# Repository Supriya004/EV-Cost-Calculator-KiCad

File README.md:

EV Cost Calculator — KiCad PCB Design

About the Project
This is a learning project created using KiCad 9 to practice electronic circuit design, PCB layout, component placement, and track routing for an EV Cost Calculator system.

Project Preview

Components Used
- Arduino UNO R3
- ACS712 current sensor
- Voltage sensor connector
- Temperature sensor connector
- 16x2 I²C LCD connector
- Relay
- LEDs and resistors
- Buzzer
- Push buttons

Tools Used
- KiCad 9 — schematic design and PCB layout

Project Status
The schematic and PCB layout were created for learning and practice. Some connections remain unrouted, so this design is **not a manufacturing-ready PCB**.

Files
-`cost_calculator.kicad_sch` — circuit schematic
- `cost_calculator.kicad_pcb` — PCB layout
- `cost_calculator.kicad_pro` — KiCad project settings

Created as a hands-on electronics design learning project.

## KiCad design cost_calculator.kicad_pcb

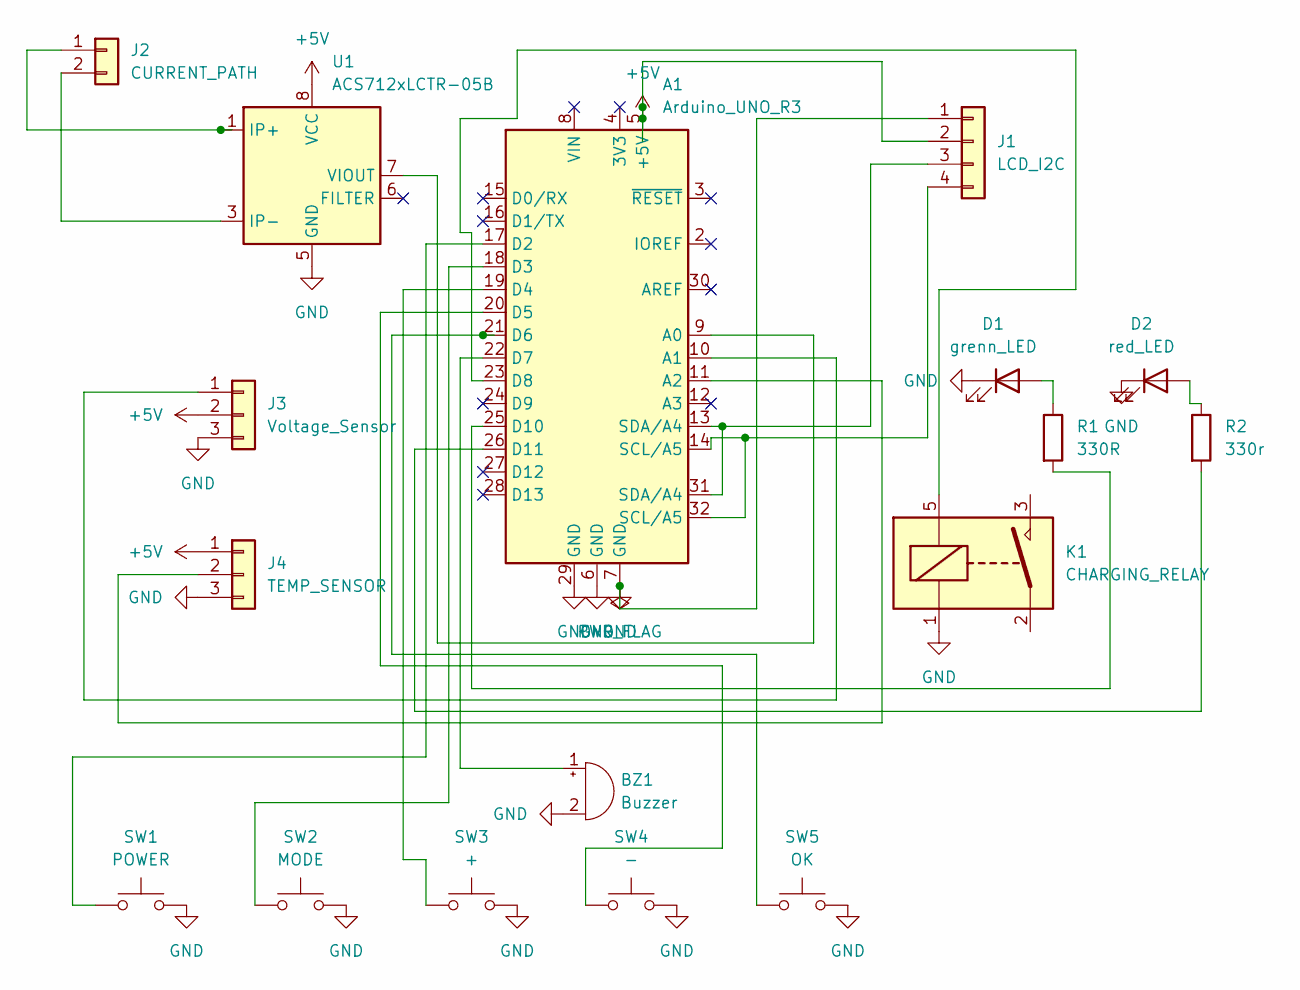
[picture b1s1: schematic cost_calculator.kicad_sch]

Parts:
A1: Arduino_UNO_R3; Arduino_UNO_R3_WithMountingHoles
BZ1: Buzzer; Buzzer_12x9.5RM7.6
D1: grenn_LED; LED_D5.0mm
D2: red_LED; LED_D5.0mm
J1: LCD_I2C; PinHeader_1x04_P2.54mm_Vertical
J2: CURRENT_PATH; PinHeader_1x02_P2.54mm_Vertical
J3: Voltage_Sensor; PinHeader_1x03_P2.54mm_Vertical
J4: TEMP_SENSOR; PinHeader_1x03_P2.54mm_Vertical
K1: CHARGING_RELAY; Relay_SPST_Omron-G5Q-1A
R1: 330R; R_Axial_DIN0207_L6.3mm_D2.5mm_P10.16mm_Horizontal
R2: 330r; R_Axial_DIN0207_L6.3mm_D2.5mm_P10.16mm_Horizontal
SW1: POWER; SW_PUSH_6mm
SW2: MODE; SW_PUSH_6mm
SW3: +; SW_PUSH_6mm
SW4: -; SW_PUSH_6mm
SW5: OK; SW_PUSH_6mm
U1: ACS712xLCTR-05B; SOIC-8_3.9x4.9mm_P1.27mm

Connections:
+5V: A1.5 (+5V), J1.2, J3.2, J4.1, U1.8 (VCC)
GND: A1.6 (GND), A1.7 (GND), A1.29 (GND), BZ1.2 (-), D1.1 (K), D2.1 (K), J1.1, J3.3, J4.3, K1.1, SW1.2, SW2.2, SW3.2, SW4.2, SW5.2, U1.5 (GND)
unnamed: A1.9 (A0), U1.7 (VIOUT)
unnamed: A1.10 (A1), J3.1
unnamed: A1.11 (A2), J4.2
unnamed: A1.17 (D2), SW1.1
unnamed: A1.18 (D3), SW2.1
unnamed: A1.19 (D4), SW3.1
unnamed: A1.20 (D5), SW4.1
unnamed: A1.21 (D6), SW5.1
unnamed: A1.22 (D7), BZ1.1 (+)
unnamed: A1.23 (D8), K1.5
unnamed: A1.25 (D10), R1.2
unnamed: A1.26 (D11), R2.2
unnamed: D1.2 (A), R1.1
unnamed: D2.2 (A), R2.1
unnamed: A1.13 (SDA/A4), A1.31 (SDA/A4), J1.3
unnamed: A1.14 (SCL/A5), A1.32 (SCL/A5), J1.4
unnamed: J2.1, U1.1 (IP+), U1.2 (IP+)
unnamed: J2.2, U1.3 (IP-), U1.4 (IP-)

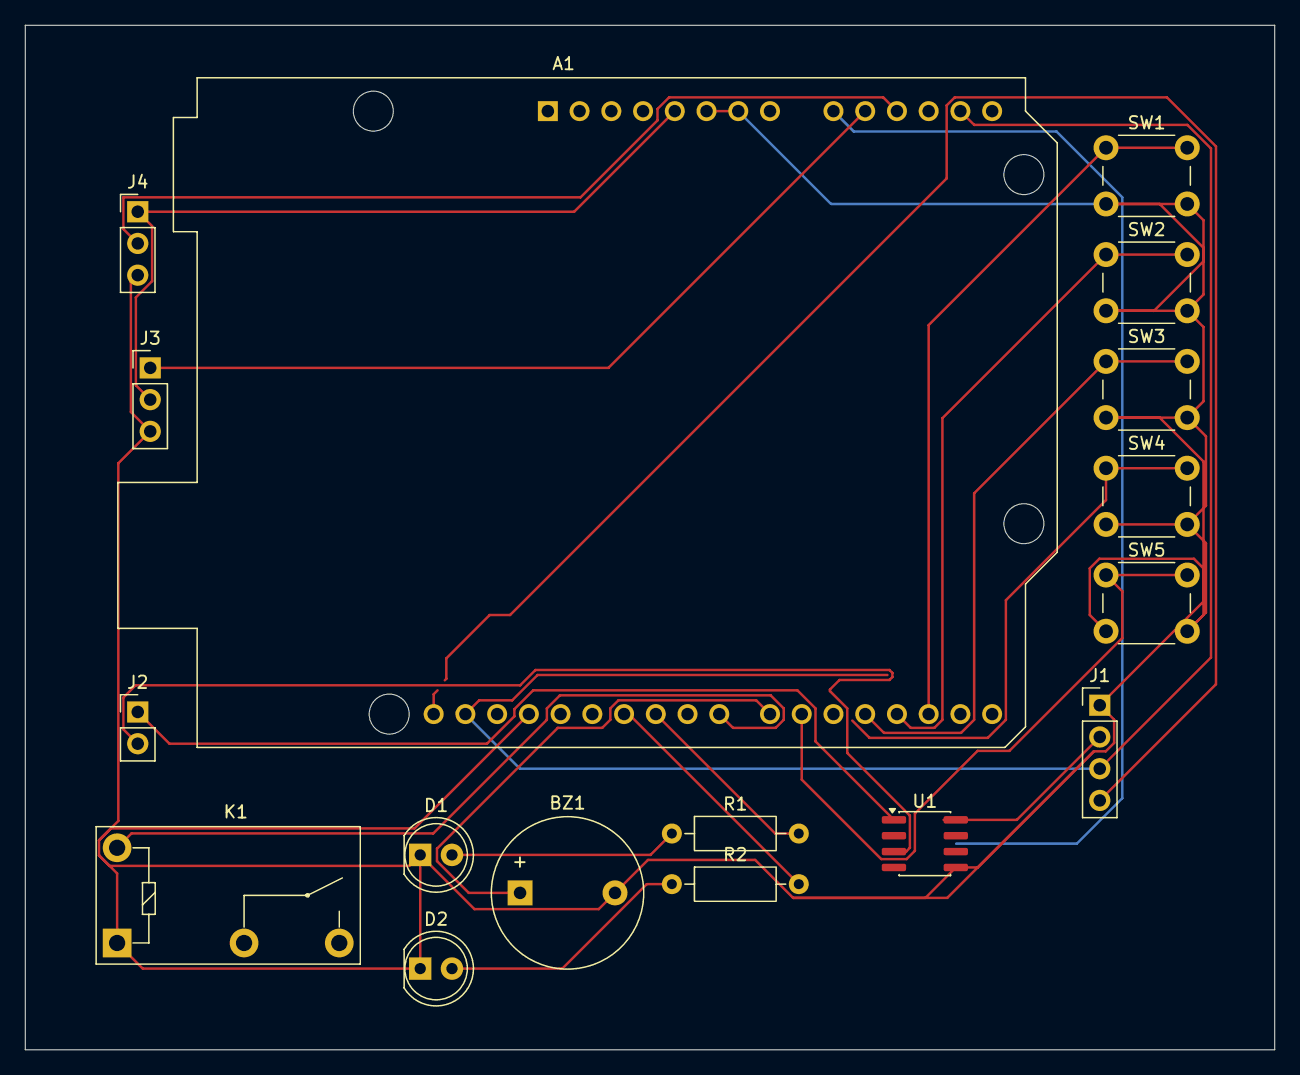
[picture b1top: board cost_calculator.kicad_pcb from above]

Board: 2 copper layers, 100.0 x 82.0 mm, 17 parts (0 on the bottom side), 20 nets.
